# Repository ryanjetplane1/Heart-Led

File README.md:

# Heart-Led
Heart Led is an interactive LED display using a 555 timer circuit with speed controlled by a potentiometer
<div></div>

This project was made for hackclub as a starter design for learning pcbs. The project took about 5 hours and was very fun to learn and is great to use instead of messy wiring.

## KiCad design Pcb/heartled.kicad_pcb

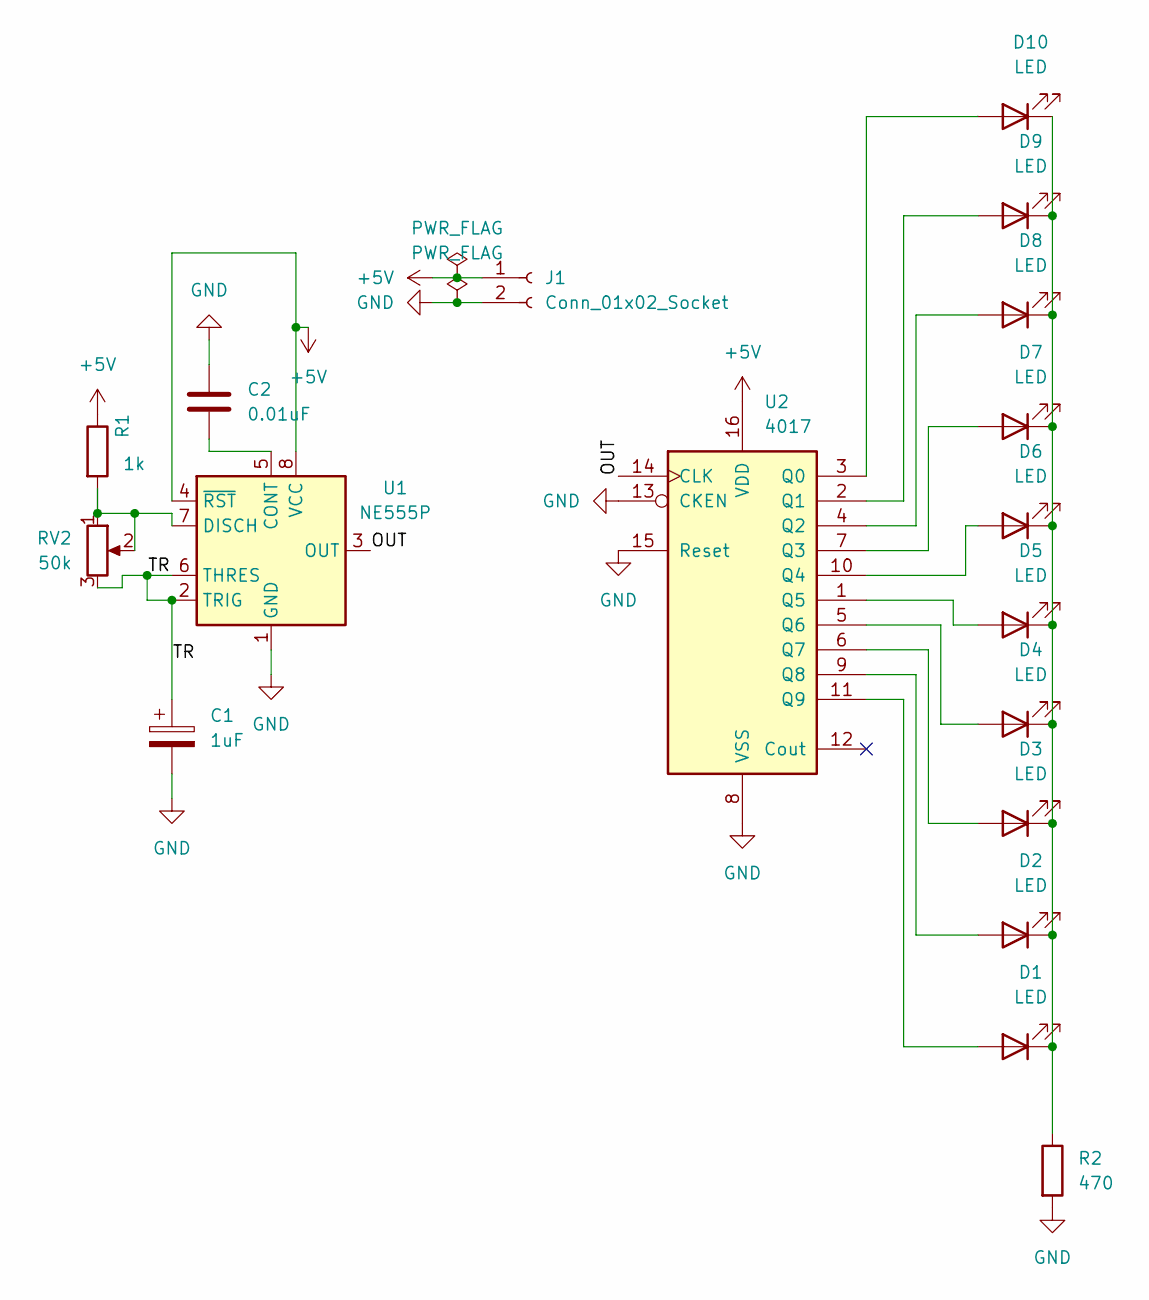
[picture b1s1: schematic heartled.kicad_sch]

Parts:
C1: 1uF; CP_Radial_D5.0mm_P2.00mm
C2: 0.01uF; C_Disc_D3.0mm_W1.6mm_P2.50mm
D1, D2, D3, D4, D5, D6, D7, D8, D9, D10: LED; LED_D5.0mm
J1: Conn_01x02_Socket; PinHeader_1x02_P2.54mm_Vertical
R1: 1k; R_Axial_DIN0207_L6.3mm_D2.5mm_P7.62mm_Horizontal
R2: 470; R_Axial_DIN0207_L6.3mm_D2.5mm_P7.62mm_Horizontal
RV2: 50k; Potentiometer_Bourns_3386P_Vertical
U1: NE555P; DIP-8_W7.62mm
U2: 4017; DIP-16_W7.62mm

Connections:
+5V: J1.1, R1.1, U1.4 (~RST), U1.8 (VCC), U2.16 (VDD)
/OUT: U1.3 (OUT), U2.14 (CLK)
/TR: C1.1, RV2.3, U1.2 (TRIG), U1.6 (THRES)
GND: C1.2, C2.1, J1.2, R2.2, U1.1 (GND), U2.8 (VSS), U2.13 (CKEN), U2.15 (Reset)
unnamed: D1.2 (A), U2.11 (Q9)
unnamed: D1.1 (K), D2.1 (K), D3.1 (K), D4.1 (K), D5.1 (K), D6.1 (K), D7.1 (K), D8.1 (K), D9.1 (K), D10.1 (K), R2.1
unnamed: D2.2 (A), U2.9 (Q8)
unnamed: D3.2 (A), U2.6 (Q7)
unnamed: D4.2 (A), U2.5 (Q6)
unnamed: D5.2 (A), U2.1 (Q5)
unnamed: D6.2 (A), U2.10 (Q4)
unnamed: D7.2 (A), U2.7 (Q3)
unnamed: D8.2 (A), U2.4 (Q2)
unnamed: D9.2 (A), U2.2 (Q1)
unnamed: D10.2 (A), U2.3 (Q0)
unnamed: C2.2, U1.5 (CONT)
unnamed: R1.2, RV2.1, RV2.2, U1.7 (DISCH)

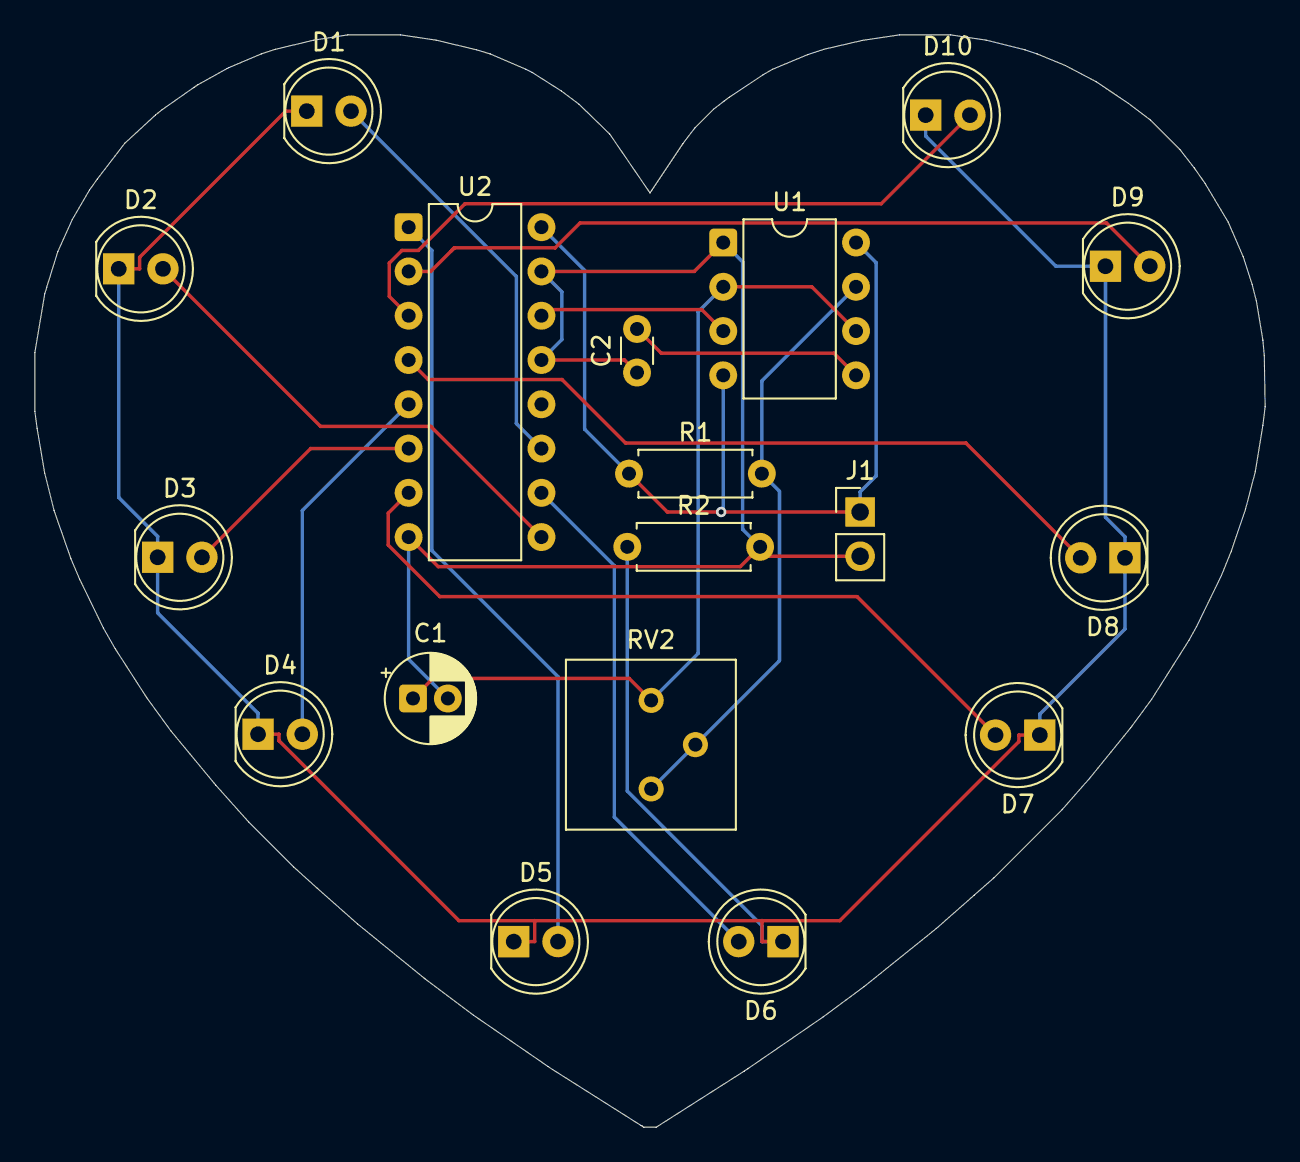
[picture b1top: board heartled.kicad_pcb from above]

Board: 2 copper layers, 70.6 x 62.7 mm, 18 parts (0 on the bottom side), 17 nets.

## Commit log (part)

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2026-04-08 Rename heartled.kicad_pcb to Pcb/heartled.kicad_pcb
2026-04-08 Rename heartled.kicad_sch to Pcb/heartled.kicad_sch
2026-04-08 Rename heartledchaser.kicad_pro to Pcb/heartledchaser.kicad_pro
